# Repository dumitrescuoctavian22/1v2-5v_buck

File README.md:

# USB-C ADJUSTABLE BUCK CONVERTER

## DESCRIPTION

A compact USB-C powered synchronous buck converter designed to provide a fixed 5 V rail and a selectable regulated output.

The project focuses on practical power electronics design, DC/DC converter selection, feedback network design, USB-C power input, PCB layout, high-current routing, mechanical design, and custom KiCad library development.

## FEATURES

* USB-C 5 V power input
* Up to 3 A continuous output capability
* Synchronous buck converter
* Selectable regulated output:

  * 1.2 V
  * 1.8 V
  * 2.5 V
  * 3.3 V
* Fixed 5 V output
* 3-pin output connector: 5 V / VOUT / GND
* Rotary switch for output voltage selection
* Input and output filtering
* 2-layer PCB
* 4 PCB mounting holes
* Custom rotary-switch footprint
* Custom rotary-switch 3D model
* Wide power traces
* Large ground plane
* USB-C power-only sink
* No USB Power Delivery required

## MAIN SPECIFICATIONS

Input:
USB-C 5 V

Converter:
TI TPS62933P

Topology:
Synchronous buck

Maximum output current:
3 A

Adjustable output:
1.2 V / 1.8 V / 2.5 V / 3.3 V

Fixed output:
5 V

Feedback reference:
0.8 V

Switching frequency:
500 kHz typical with RT floating

Inductor:
TDK VLS6045EX-6R8M
6.8 uH

PCB:
2-layer FR-4
1 oz copper

Output connector:
3-pin, 2.54 mm

Mounting holes:
4x
2.0 mm outer diameter
1.5 mm hole diameter

## OUTPUT CONNECTOR

The board uses a 3-pin output connector.

Pin 1:
5 V

Pin 2:
VOUT - adjustable regulated output

Pin 3:
GND

The 5 V output is connected to the USB-C VBUS rail.

The VOUT pin provides the regulated output selected using the rotary switch.

## USB-C INPUT

The USB-C connector is configured as a 5 V power-only sink.

CC1:
5.1 kOhm pull-down to GND

CC2:
5.1 kOhm pull-down to GND

D+:
Not connected

D-:
Not connected

SBU1:
Not connected

SBU2:
Not connected

USB Power Delivery is not used.

## POWER CONVERTER

The main regulator is the TI TPS62933P.

Key characteristics:

* 3 A continuous output capability
* 3.8 V to 30 V input range
* 0.8 V to 22 V output range
* Integrated MOSFETs
* Internal loop compensation
* Pulse-frequency modulation at light loads
* Spread-spectrum operation
* Overcurrent protection
* Overvoltage protection
* Undervoltage protection
* Undervoltage lockout
* Thermal protection

The RT pin is left floating, giving a typical switching frequency of 500 kHz.

## FEEDBACK NETWORK

The output voltage is selected using a rotary switch connected to the feedback resistor network.

Bottom feedback resistor:

* RFBB = 10.2 kOhm

Rotary switch positions:

Position 1:
RFBT = 5.1 kOhm
VOUT = 1.2 V

Position 2:
RFBT = 12.7 kOhm
VOUT = 1.8 V

Position 3:
RFBT = 21.5 kOhm
VOUT = 2.5 V

Position 4:
RFBT = 31.6 kOhm
VOUT = 3.3 V

The feedback resistors use 1% tolerance.

## INPUT FILTERING

The input filtering consists of:

* 47 uF bulk capacitor
* 10 uF ceramic capacitor
* 100 nF ceramic capacitor

The capacitors are placed close to the converter input to reduce input impedance and minimize the high-frequency switching loop.

## OUTPUT FILTERING

The output filtering consists of:

* 2 x 22 uF ceramic capacitors
* 1 x 100 nF ceramic capacitor
* 6.8 uH power inductor

The output capacitors are positioned close to the power stage.

## INDUCTOR

Part:
TDK VLS6045EX-6R8M

Value:
6.8 uH

Package:
6 x 6 x 4.5 mm

## ROTARY SWITCH

The rotary switch is used to select the feedback resistor and therefore the regulated output voltage.

Component:
Nidec Copal S-2050

The switch only carries the feedback-network current and does not carry the main output current.

## CUSTOM FOOTPRINT AND 3D MODEL

A custom KiCad footprint was created for the rotary switch.

A custom 3D model was also created for the component.

The custom library work included:

* Measuring the physical component
* Creating the through-hole pad layout
* Creating the PCB footprint
* Defining pad and courtyard dimensions
* Creating the 3D model
* Aligning the 3D model with the footprint
* Verifying the component in KiCad's 3D viewer

This allows the actual rotary switch to be accurately represented in both the PCB layout and 3D view.

## PCB DESIGN

The PCB is a 2-layer FR-4 design with 1 oz copper.

Important layout considerations include:

* Input capacitors placed close to VIN
* Short switching-current paths
* Short SW connection
* Inductor positioned close to the converter
* Output capacitors positioned close to the inductor
* Feedback routing kept away from the switching node
* Large ground plane
* Wide VIN and VOUT traces
* Additional copper around the power components for thermal management

## CURRENT ROUTING

The main power paths use wide copper traces.

Important high-current paths include:

* USB-C VBUS to the input capacitors
* Input capacitors to the TPS62933P
* TPS62933P to the inductor
* Inductor to the output capacitors
* Output capacitors to the VOUT connector

Approximately 1.5 mm wide traces are used for the main power paths where appropriate.

## MOUNTING

The PCB includes four mounting holes.

Mounting-hole geometry:

* Outer diameter: 2.0 mm
* Hole diameter: 1.5 mm

The mounting holes provide mechanical mounting points for PCB standoffs or suitable hardware.

## DESIGN GOALS

The main goals of the project were to demonstrate practical experience with:

* DC/DC converter selection
* Synchronous buck converter design
* Feedback network design
* USB-C power input
* Power component selection
* Inductor selection
* Capacitor selection
* Switching power supply layout
* Ground-plane design
* Custom KiCad footprint creation
* Custom 3D model creation
* Mechanical PCB design

## TOOLS

* KiCad
* Schematic capture
* PCB layout
* PCB routing
* Custom footprint creation
* Custom 3D model creation

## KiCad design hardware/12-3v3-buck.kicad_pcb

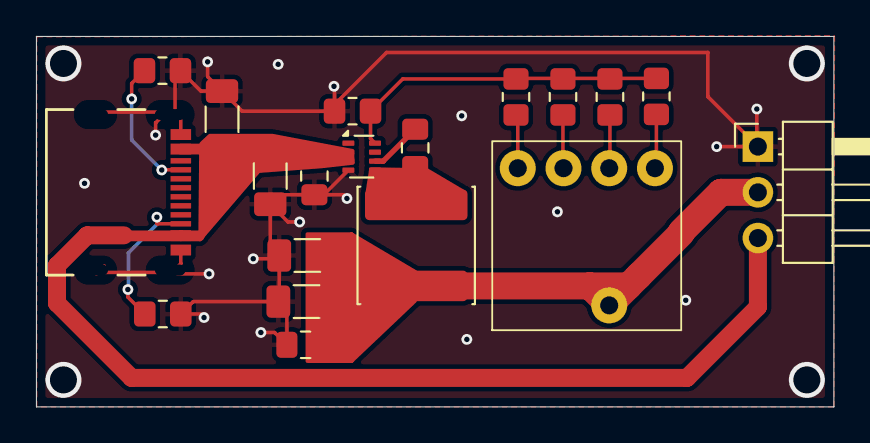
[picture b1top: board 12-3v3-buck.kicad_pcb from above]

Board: 2 copper layers, 44.3 x 20.6 mm, 19 parts (0 on the bottom side), 12 nets.

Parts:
C1: 10u; C_1206_3216Metric_Pad1.33x1.80mm_HandSolder
C2, C4, C7: u1; C_0805_2012Metric_Pad1.18x1.45mm_HandSolder
C3: 47u; C_1206_3216Metric_Pad1.33x1.80mm_HandSolder
C5, C6: 22u; C_1206_3216Metric_Pad1.33x1.80mm_HandSolder
J1: TYPE-C16PIN; CONN16_C16PIN_SHN
J2: Conn_01x03_Pin; PinHeader_1x03_P2.54mm_Horizontal
L1: 6u8; L_APV_ANR6045
R1, R2, R7: 5k1; R_0805_2012Metric_Pad1.20x1.40mm_HandSolder
R3: 10k2; R_0805_2012Metric_Pad1.20x1.40mm_HandSolder
R4: 31k6; R_0805_2012Metric_Pad1.20x1.40mm_HandSolder
R5: 21k5; R_0805_2012Metric_Pad1.20x1.40mm_HandSolder
R6: 12k7; R_0805_2012Metric_Pad1.20x1.40mm_HandSolder
U1: SP4T Rotary Switch S-2051
U2: TPS62933P; SOT-583-8

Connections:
GNDREF: C1.2, C2.2, C3.2, C5.2, C6.2, C7.2, J1.A1 (GND), J1.A12 (GND), J1.B1 (GND), J1.B12 (GND), J2.1, R1.2, R2.2, R3.1, U2.4 (GND)
unnamed: J1.A5 (CC1), R2.1
unnamed: J1.B5 (CC2), R1.1
unnamed: R4.1, U1.1
unnamed: R5.1, U1.2
unnamed: R6.1, U1.3
unnamed: R7.1, U1.4
unnamed: C4.1, U2.6 (BST)
unnamed: R3.2, R4.2, R5.2, R6.2, R7.2, U2.8 (FB)
unnamed: C4.2, L1.1, U2.5 (SW)
VBUS: C1.1, C2.1, C3.1, J1.A4 (VBUS), J1.A9 (VBUS), J1.B4 (VBUS), J1.B9 (VBUS), J2.3, U2.2 (EN), U2.3 (VIN)
Vout: C5.1, C6.1, C7.1, J2.2, L1.2, U1.5 (C)
